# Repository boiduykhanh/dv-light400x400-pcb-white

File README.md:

## Thanh led trắng
# Yêu cầu
  Kích thước board 280x5mm

# Sơ đổ nguyên lý:

## Mạch in

## 3D

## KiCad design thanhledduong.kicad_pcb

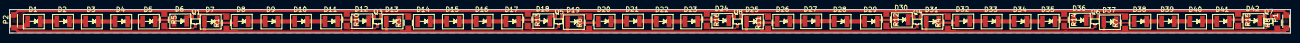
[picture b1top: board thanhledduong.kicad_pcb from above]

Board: 2 copper layers, 275.0 x 5.0 mm, 65 parts (0 on the bottom side), 58 nets.

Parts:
D1, D2, D3, D4, D5, D6, D7, D8, D9, D10, D11, D12, D13, D14, D15, D16, D17, D18, D19, D20, D21, D22, D23, D24, D25, D26, D27, D28, D29, D30, D31, D32, D33, D34, D35, D36, D37, D38, D39, D40, D41, D42: LED; led3528
P1, P2: CONN_01X02; con2
Q1, Q3, Q4, Q5, Q6, Q7, Q8: Q_NPN_BCE; SOT-323
R1, R3, R4, R5, R6, R7, R8, R10, R11, R12, R13, R14, R15, R16: R; R_0805_HandSoldering

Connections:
+24V: D1.2, D7.2, D13.2, D19.2, D25.2, D31.2, D37.2, P1.1, P2.1, R1.1, R3.1, R4.1, R6.1, R7.1, R8.1, R11.1
GND: P1.2, P2.2, R5.1, R10.1, R12.1, R13.1, R14.1, R15.1, R16.1
unnamed: D1.1, D2.2
unnamed: D2.1, D3.2
unnamed: D3.1, D4.2
unnamed: D4.1, D5.2
unnamed: D5.1, D6.2
unnamed: D6.1, Q1.2
unnamed: D7.1, D8.2
unnamed: D8.1, D9.2
unnamed: D10.1, D11.2
unnamed: D9.1, D10.2
unnamed: D11.1, D12.2
unnamed: D12.1, Q3.2
unnamed: D13.1, D14.2
unnamed: D14.1, D15.2
unnamed: D15.1, D16.2
unnamed: D16.1, D17.2
unnamed: D17.1, D18.2
unnamed: D18.1, Q5.2
unnamed: D19.1, D20.2
unnamed: D20.1, D21.2
unnamed: D21.1, D22.2
unnamed: D22.1, D23.2
unnamed: D23.1, D24.2
unnamed: D24.1, Q8.2
unnamed: D25.1, D26.2
unnamed: D26.1, D27.2
unnamed: D27.1, D28.2
unnamed: D28.1, D29.2
unnamed: D29.1, D30.2
unnamed: D30.1, Q4.2
unnamed: D31.1, D32.2
unnamed: D32.1, D33.2
unnamed: D33.1, D34.2
unnamed: D34.1, D35.2
unnamed: D35.1, D36.2
unnamed: D36.1, Q6.2
unnamed: D37.1, D38.2
unnamed: D38.1, D39.2
unnamed: D39.1, D40.2
unnamed: D40.1, D41.2
unnamed: D41.1, D42.2
unnamed: D42.1, Q7.2
unnamed: Q1.1, R1.2
unnamed: Q1.3, R5.2
unnamed: Q3.1, R3.2
unnamed: Q3.3, R10.2
unnamed: Q4.1, R4.2
unnamed: Q4.3, R12.2
unnamed: Q5.1, R6.2
unnamed: Q5.3, R13.2
unnamed: Q6.1, R7.2
unnamed: Q6.3, R14.2
unnamed: Q7.1, R8.2
unnamed: Q7.3, R15.2
unnamed: Q8.1, R11.2
unnamed: Q8.3, R16.2

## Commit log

2016-06-10 version 1
2016-06-13 finish project
